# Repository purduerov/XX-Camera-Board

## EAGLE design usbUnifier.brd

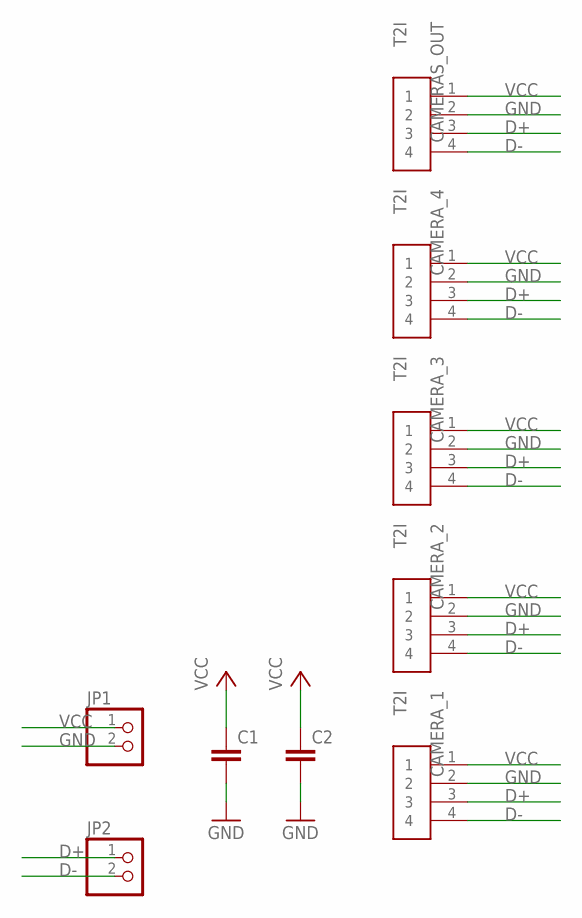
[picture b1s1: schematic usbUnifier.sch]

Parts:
C1, C2: C-EUC0603; C0603
CAMERAS_OUT: T2I
CAMERA_1, CAMERA_2, CAMERA_3, CAMERA_4: T2I
JP1, JP2: PINHD-1X2; 1X02

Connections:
D+: CAMERAS_OUT.3, CAMERA_1.3, CAMERA_2.3, CAMERA_3.3, CAMERA_4.3, JP2.1
D-: CAMERAS_OUT.4, CAMERA_1.4, CAMERA_2.4, CAMERA_3.4, CAMERA_4.4, JP2.2
GND: C1.2, C2.2, CAMERAS_OUT.2, CAMERA_1.2, CAMERA_2.2, CAMERA_3.2, CAMERA_4.2, JP1.2
VCC: C1.1, C2.1, CAMERAS_OUT.1, CAMERA_1.1, CAMERA_2.1, CAMERA_3.1, CAMERA_4.1, JP1.1

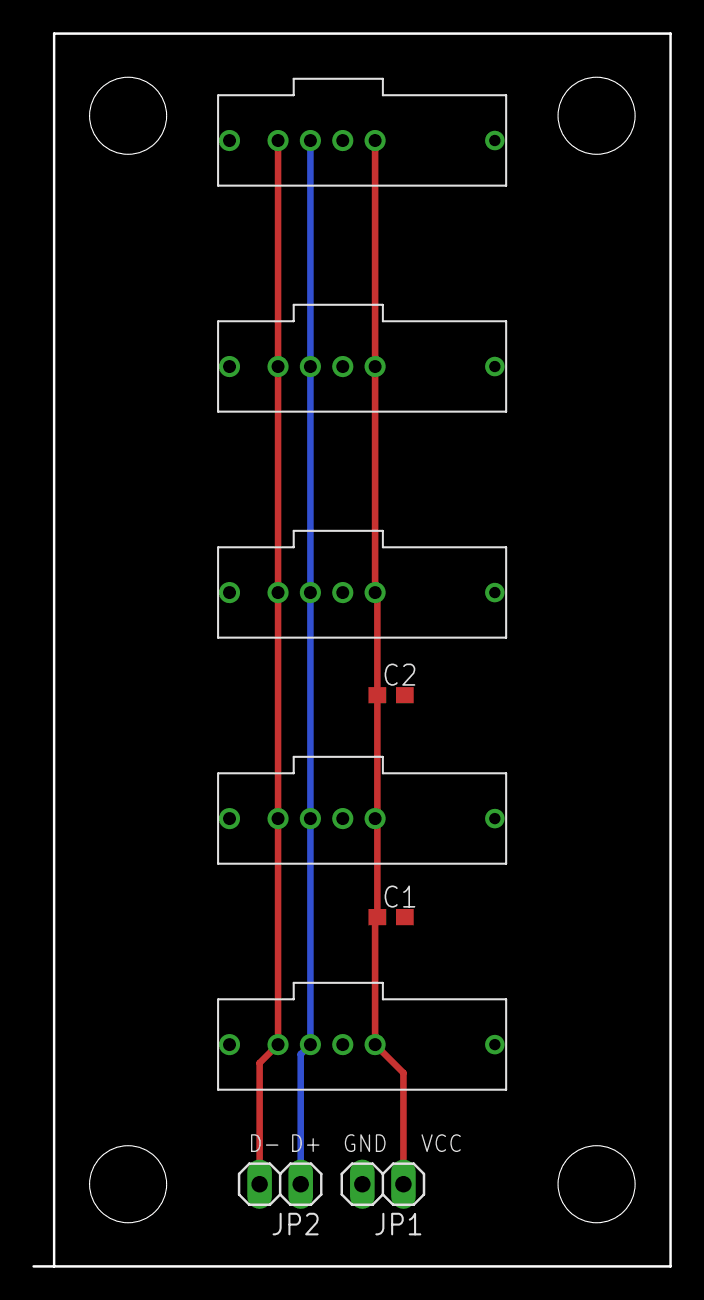
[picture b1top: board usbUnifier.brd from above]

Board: 2 copper layers, 39.4 x 76.2 mm, 9 parts (0 on the bottom side), 4 nets.

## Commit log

2017-10-15 Added gitignore
2017-10-21 Initial layout of usb camera line combiner
2017-11-02 Added drill holes
